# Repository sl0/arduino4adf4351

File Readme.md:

# ArduinoNano for ADF4351

## Handy tool for flexible configuration of ADF4351

An Arduino Nano is used to set ADF4351 Registers to determine the
Synthesizers output frequency.

### Software License

The ard4adf.ino file is licensed under the terms of
GNU General Public License version 3 or later.

For KiCAD the footprint and library modules of the voltage-regulator
chips are found on the net with unknown licenses, so they are not
included here. Files in the kicad directory are 'Open Source' under
the terms of the definition for Open Source Hardware Association.

    http://www.oshwa.org/definition/

## Arduino sketch

Host (DK2KA) build various Synthesizer solutions – based on
handwired hardware PoC for GHz Beacons, AO 100 and 10 GHz EME HAM
Radio Devices – Arduino Sketches included.
Wolf (DF7KB) suggested modifications to ease assembling the PCBs,
especially to create a backpack solution that fits exactly onto
the Synthesizer breakout board.

A solution to select a variety of frequencies from the Synthesizer
has been added.  Aim was to generate Local Oscillator frequencies
for Transverters, synchronizing them with GPS and therefore
preparing the HAM Equipment for frequency accuracy and weak signal
operations.

The Sketch was transformed into an „easyly readable code“ to allow
adaptations on the fly.

Finally the ADF4351 evaluation board was extended with the Arduino
NANO Hardware to create a handy solution to set the synthezisers
registers. At the same time debugging elements have been added.

### Compiling and debugging - Sketch: ard4adf.ino

The ard4adf.ino can be compiled and loaded into an Arduino-Nano.

#### Debug via Serial Monitor

For testing just use the serial monitor of ardunio-IDE, if
the line

    //#define DEBUG_VIA_SERIAL

is uncommented at compile time.

#### Debug via Blinking Arduino Led

Another useful debugging feature is implented by using the led on the
arduino board. Repeating one second led-on mean the LE pin is low, so
ADF4351 is signaling PLL sync is lost. Short flickers should be
counted after a three second pause, the number indicates the jumpers
reading and so you can easily read the frequency on ADF4351 outputs
(in a binary way).

There are 3 jumpers read as 3 bits, so its 0 .. 7, 8 possible settings.
Jumper set means bit is set to low. Jumper not set means bit is set to
high.

    1 flicker and 3 sec pause <==> jumpers are evaluated to 0.
    2 flickers and 3 sec pause <==> jumpers are evaluated to 1
    ...
    8 flickers and 3 sec pause <==> jumper s are evaluated to 7

The flickering is always on.

## KiCAD-PCB

The KiCAD schema and PCB-layout may be found in the directory kicad.
**ADM7150ARDZ-3.3** and **ADM7150ARDZ-5.0** are voltage regulators
used to achieve  low noise power supplies on the arduino and the
ADF4351 chips. The board may be powered with some 6 to 7 V DC. It
is assembled in a mixture of conventional and SMD parts.

Have fun!

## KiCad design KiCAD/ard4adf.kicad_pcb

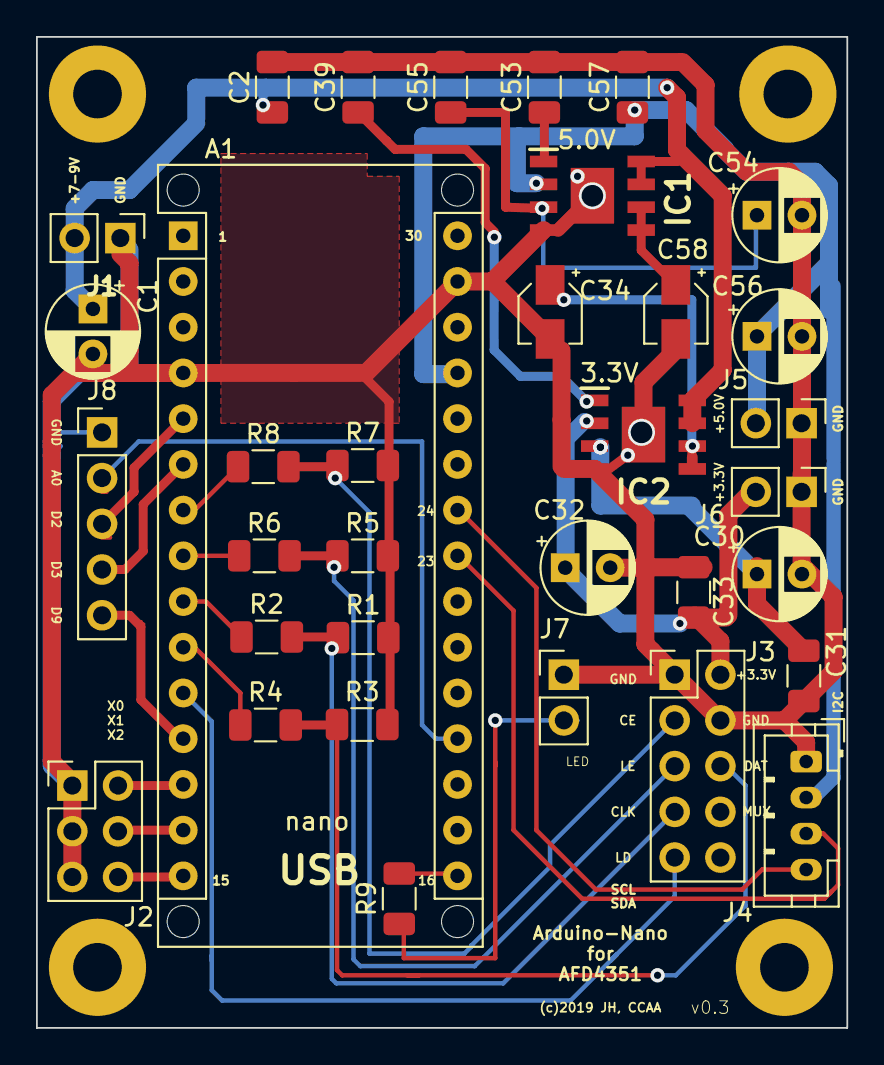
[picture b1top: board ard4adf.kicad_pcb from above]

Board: 2 copper layers, 45.0 x 55.1 mm, 34 parts (0 on the bottom side), 30 nets.

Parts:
A1: Arduino_Nano_v3.x; Arduino_Nano_WithMountingHoles
C1, C30, C32, C54, C56: 47uF; CP_Radial_D5.0mm_P2.50mm
C2, C31, C33, C39, C53, C55, C57: 10nF; C_1206_3216Metric
C34, C58: 1uF; CP_Elec_3x5.3
IC1: ADM7150ARDZ-5.0; SOIC127P600X175-9N
IC2: ADM7150ARDZ-3.3; SOIC127P600X175-9N
J1, J5, J6, J7: Conn_01x02_Male; PinHeader_1x02_P2.54mm_Vertical
J2: Conn_02x03_Odd_Even; PinHeader_2x03_P2.54mm_Vertical
J3: Conn_02x05_Top_Bottom; PinHeader_2x05_P2.54mm_Vertical
J4: Conn_01x04_Male; JST_PH_B4B-PH-K_1x04_P2.00mm_Vertical
J8: Conn_01x05_Male; PinHeader_1x05_P2.54mm_Vertical
R1, R3, R5, R7: 3k3; R_1206_3216Metric
R2, R4, R6, R8: 1k5; R_1206_3216Metric
R9: 220; R_1206_3216Metric

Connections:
GND: A1.4, A1.29, C1.2, C2.2, C30.2, C31.2, C32.2, C33.2, C34.2, C39.2, C53.2, C54.2, C55.2, C56.2, C57.2, C58.2, IC1.4, IC1.9, IC2.4, IC2.9, J1.1, J2.1, J2.3, J2.5, J3.1, J3.4, J4.1, J5.1, J6.1, J7.1, J8.1, R1.2, R3.2, R5.2, R7.2
unnamed: A1.5, J8.3
unnamed: A1.6, J8.4
unnamed: A1.7, R8.1
unnamed: A1.8, R6.1
unnamed: A1.9, R2.1
unnamed: A1.10, R4.1
unnamed: A1.11, J3.9
unnamed: A1.12, J8.5
unnamed: A1.13, J2.2
unnamed: A1.14, J2.4
unnamed: A1.15, J2.6
unnamed: A1.16, R9.2
unnamed: A1.19, J8.2
unnamed: A1.23, J4.3
unnamed: A1.24, J4.4
unnamed: A1.27, C56.1, C57.1, IC1.2, J4.2, J5.2
unnamed: C1.1, C2.1, IC1.7, IC1.8, IC2.7, IC2.8, J1.2
unnamed: C30.1, C31.1, IC2.3
unnamed: C32.1, C33.1, IC2.2, J3.2, J6.2
unnamed: C34.1, IC2.5, IC2.6
unnamed: C39.1, IC2.1
unnamed: C53.1, IC1.1
unnamed: C54.1, C55.1, IC1.3
unnamed: C58.1, IC1.5, IC1.6
unnamed: J3.3, R7.1, R8.2
unnamed: J3.5, R5.1, R6.2
unnamed: J3.6, R3.1, R4.2
unnamed: J3.7, R1.1, R2.2
unnamed: J7.2, R9.1

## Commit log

2019-11-28 Initial commit
    GNU General Public License is included
2019-11-29 Adds first arduino sketch to control the beast
    It is working as designed first time on 2019-11-28 (very first bugs fixed)
2019-11-29 Adds PCB prototype and schema
    Included: 5.0V and 3.3V regulators and a socket for an Arduino-Nano
2019-11-29 Adds Readme.md and corresponding pictures
2019-12-01 Ensure Arduino-IDE is satisfied: changed dir-name
2019-12-01 Changes Jumper logic to positive
    Just to behave like expected:
    Jumper set means logical 1 now
    Jumper not set means logical 0 now
2019-12-01 Disables DEBUG_VIA_SERIAL again
2019-12-01 Adds R(220) and output-pins J7 for external LED
2019-12-11 Adapt and update frequencies to external 10MHz reference
2019-12-12 Updates PCB to newest order
    Adds 5-pin connector: A0, D2, D3, D9
2019-12-12 Updates PCB picture (used in Readme.md)
2021-03-14 Upgrades to Kicad 5.1.9 backport from sid
2021-03-14 Changes first two freqs to 1728.000 and 1748.250 MHz
    Take these times 6 to check 3cm band LNBs

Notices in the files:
KiCAD/ard4adf.kicad_pcb:
(c)2019 JH, CCAA
